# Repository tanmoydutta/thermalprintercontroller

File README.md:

<h1>Thermal Printer Controller Hardware</h1>

Anthe is a Wireless Thermal Printer controller over WiFi and Bluetooth. It is based on ESP32-C3-FH4 Microcontroller. 

Features include - 
- Programmable WiFi and Bluetooth Connectivity for Thermal Printer
- Onboard logic level shifter for 5V Printer operation.
- Onboard Printer power supply connector
- USB-C Port for programming
- Onboard programmable RGB and normal LED indicators
- Onboard WiFi and Bluetooth Antenna
- Compact size 
- Powered by ESP32-C3-FH4 Microcontroller

Build your own Printer driver using Adafruit Thermal Printer library and extend connectivity over WiFi and Bluetooth.

This is an OSHWA certified hardware - 
<p align="center">
  
</p>

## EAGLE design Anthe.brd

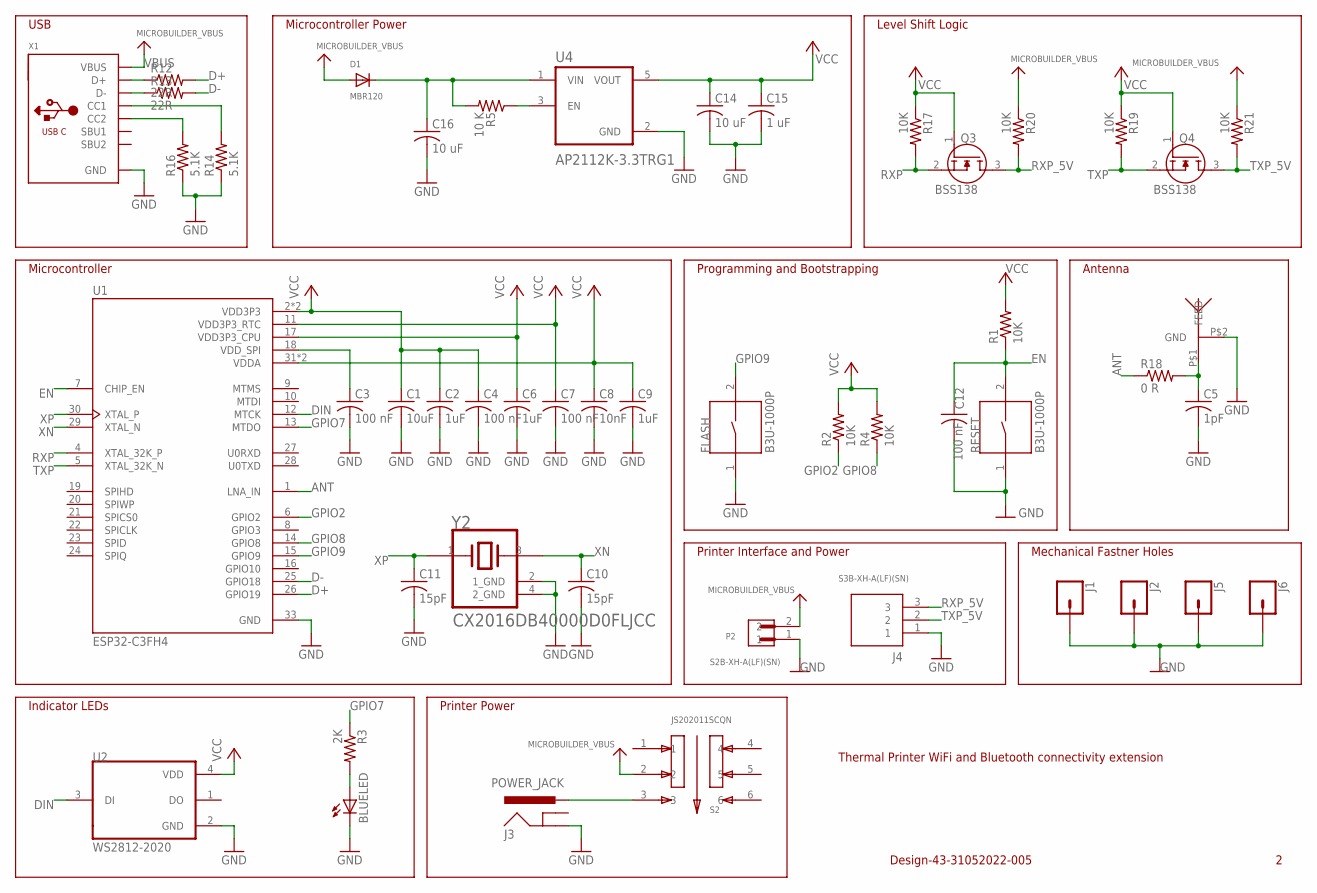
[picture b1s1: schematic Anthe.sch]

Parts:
BLUELED: LEDCHIPLED_0603; CHIPLED_0603
C1: 10uF; C0402
C2, C6, C9: 1uF; C0402
C3, C4, C7, C12: 100 nF; C0402
C5: 1pF; C0402
C8: 10nF; C0402
C10, C11: 15pF; C0402
C14, C16: 10 uF; C0402
C15: 1 uF; C0402
D1: MBR120; SOD-123
FLASH: B3U-1000P; SW_B3U-1000P
J1, J2, J5, J6: CONN_01PTH_2MM; 1X01_2MM
J3: POWER_JACK; POWER_JACK_PTH
J4: S3B-XH-A(LF)(SN); JST_S3B-XH-A(LF)(SN)
P2: S2B-XH-A(LF)(SN); JST_S2B-XH-A(LF)(SN)
Q3, Q4: BSS138; SOT95P240X120-3N
R1, R2, R4, R17, R19, R20, R21: 10K; R0402
R3: 2K; R0402
R5: 10 K; R0402
R12, R13: 22R; R0402
R14, R16: 5.1K; R0402
R18: 0 R; R0402
RESET: B3U-1000P; SW_B3U-1000P
S2: JS202011SCQN; SW_JS202011SCQN
U1: ESP32-C3FH4; QFN50P500X500X90-33N
U2: WS2812-2020; LED_WS2812-2020
U4: AP2112K-3.3TRG1; SOT95P285X140-5N
U$3: PCB_ANTENNA_WIFI; WIFI_ANTENNA
X1: MICROBUILDER_USB_C; MICROBUILDER_USB_C_CUSB31-CFM2AX-01-X
Y2: KYOCERA_INTERNATIONAL_INC._ELECTRONIC_COMPONENTS_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; KYOCERA_INTERNATIONAL_INC._ELECTRONIC_COMPONENTS_CX2016DB40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

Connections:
ANT: R18.1, U1.1 (LNA_IN)
D+: R12.2, U1.26 (GPIO19)
D-: R13.2, U1.25 (GPIO18)
DIN: U1.12 (MTCK), U2.3 (DI)
EN: C12.1, R1.1, RESET.2, U1.7 (CHIP_EN)
GND: BLUELED.C, C1.2, C2.2, C3.2, C4.2, C5.2, C6.2, C7.2, C8.2, C9.2, C10.2, C11.2, C12.2, C14.2, C15.2, C16.2, FLASH.1, J1.1, J2.1, J3.GND, J4.1, J5.1, J6.1, P2.1, R14.1, R16.1, RESET.1, U1.33 (GND), U2.2 (GND), U4.2 (GND), U$3.P$2 (GND), X1.A1B12 (GND), X1.B1A12 (GND), Y2.2 (1_GND), Y2.4 (2_GND)
GPIO2: R2.1, U1.6 (GPIO2)
GPIO7: R3.1, U1.13 (MTDO)
GPIO8: R4.1, U1.14 (GPIO8)
GPIO9: FLASH.2, U1.15 (GPIO9)
unnamed: J3.PWR, S2.3
unnamed: C5.1, R18.2, U$3.P$1 (FEED)
unnamed: C3.1, U1.18 (VDD_SPI)
unnamed: BLUELED.A, R3.2
unnamed: R12.1, X1.A6 (D+), X1.B6 (D+)
unnamed: C16.1, D1.C, R5.2, U4.1 (VIN)
unnamed: R13.1, X1.A7 (D-), X1.B7 (D-)
unnamed: R14.2, X1.A5 (CC1)
unnamed: R16.2, X1.B5 (CC2)
unnamed: R5.1, U4.3 (EN)
RXP: Q3.2 (S), R17.2, U1.4 (XTAL_32K_P)
RXP_5V: J4.3, Q3.3 (D), R20.2
TXP: Q4.2 (S), R19.2, U1.5 (XTAL_32K_N)
TXP_5V: J4.2, Q4.3 (D), R21.2
VBUS: D1.A, P2.2, R20.1, R21.1, S2.2, X1.A4B9 (VBUS), X1.B4A9 (VBUS)
VCC: C1.1, C2.1, C4.1, C6.1, C7.1, C8.1, C9.1, C14.1, C15.1, Q3.1 (G), Q4.1 (G), R1.2, R2.2, R4.2, R17.1, R19.1, U1.2 (VDD3P3), U1.3 (VDD3P3), U1.11 (VDD3P3_RTC), U1.17 (VDD3P3_CPU), U1.31 (VDDA), U1.32 (VDDA), U2.4 (VDD), U4.5 (VOUT)
XN: C10.1, U1.29 (XTAL_N), Y2.3
XP: C11.1, U1.30 (XTAL_P), Y2.1

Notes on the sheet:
USB
Microcontroller Power
Microcontroller
Level Shift Logic
Programming and Bootstrapping
Antenna
Indicator LEDs
Thermal Printer WiFi and Bluetooth connectivity extension
Design-43-31052022-005
Printer Power
Printer Interface and Power
Mechanical Fastner Holes

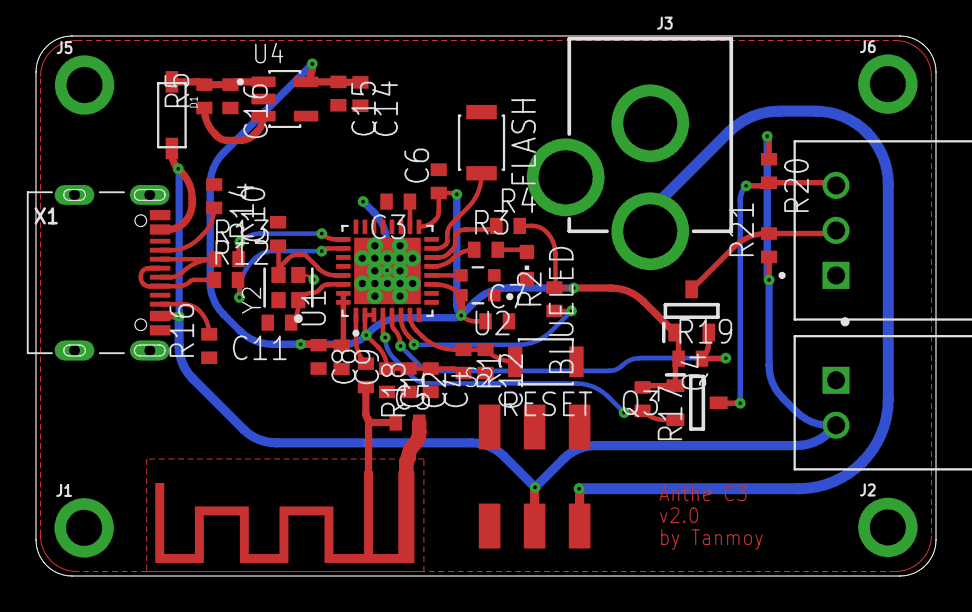
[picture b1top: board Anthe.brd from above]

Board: 2 copper layers, 50.0 x 30.0 mm, 49 parts (0 on the bottom side), 28 nets.

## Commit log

2022-06-01 Add files via upload
    EAGLE schematics and PCB board files. PDF version of schematics and board design file.
2022-06-01 Added images
2022-06-01 Readme document
    Detail description of features
2022-06-01 Adjujstments
2022-06-01 Further adjustments
2025-06-23 File updates to design
2025-06-26 Adding OSHWA certification mark
2025-06-26 Update README.md
    OSHWA certification mark

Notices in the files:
parts and their libraries:
SparkFun-Connectors: Licensing: Creative Commons ShareAlike 4.0 International - https://creativecommons.org/licenses/by-sa/4.0
